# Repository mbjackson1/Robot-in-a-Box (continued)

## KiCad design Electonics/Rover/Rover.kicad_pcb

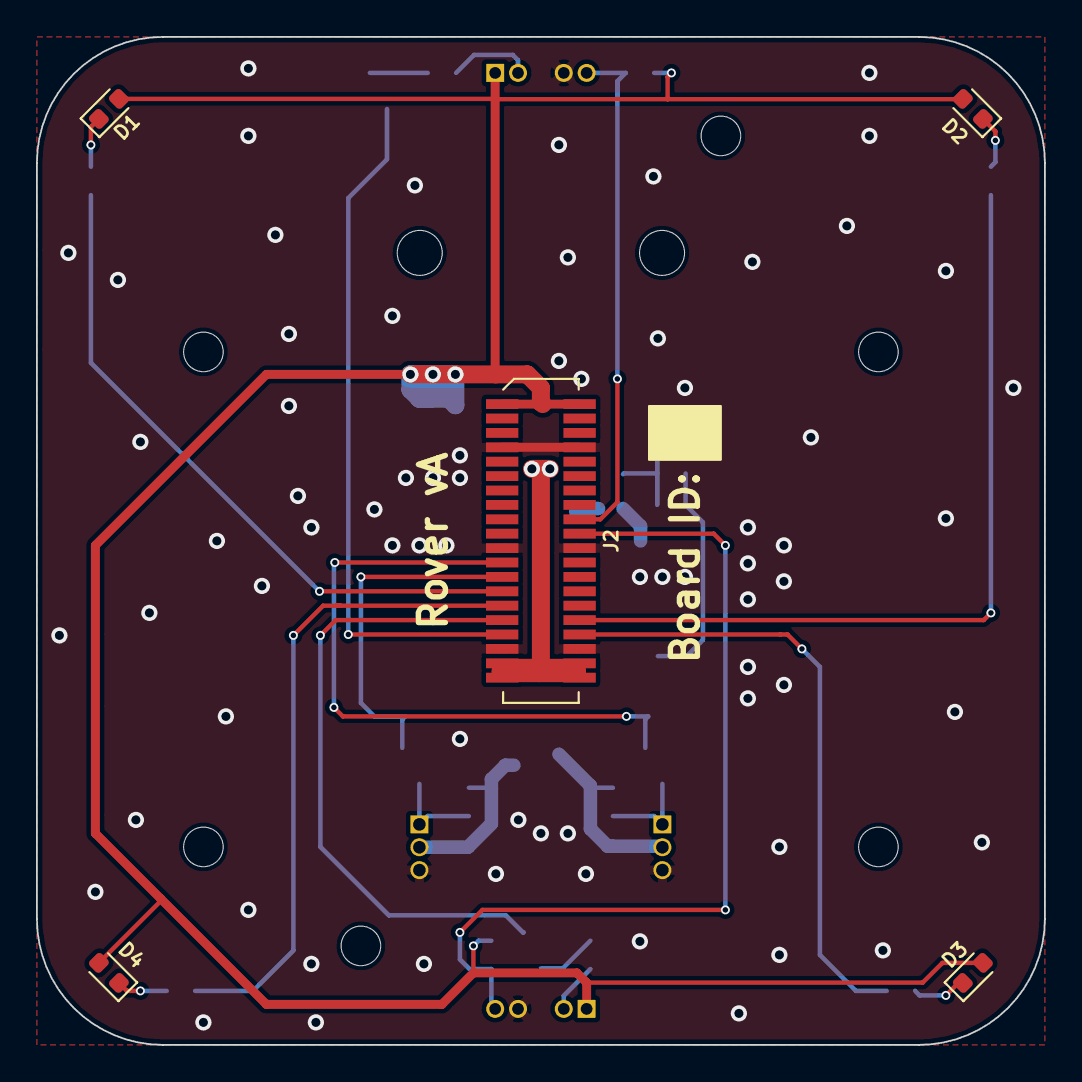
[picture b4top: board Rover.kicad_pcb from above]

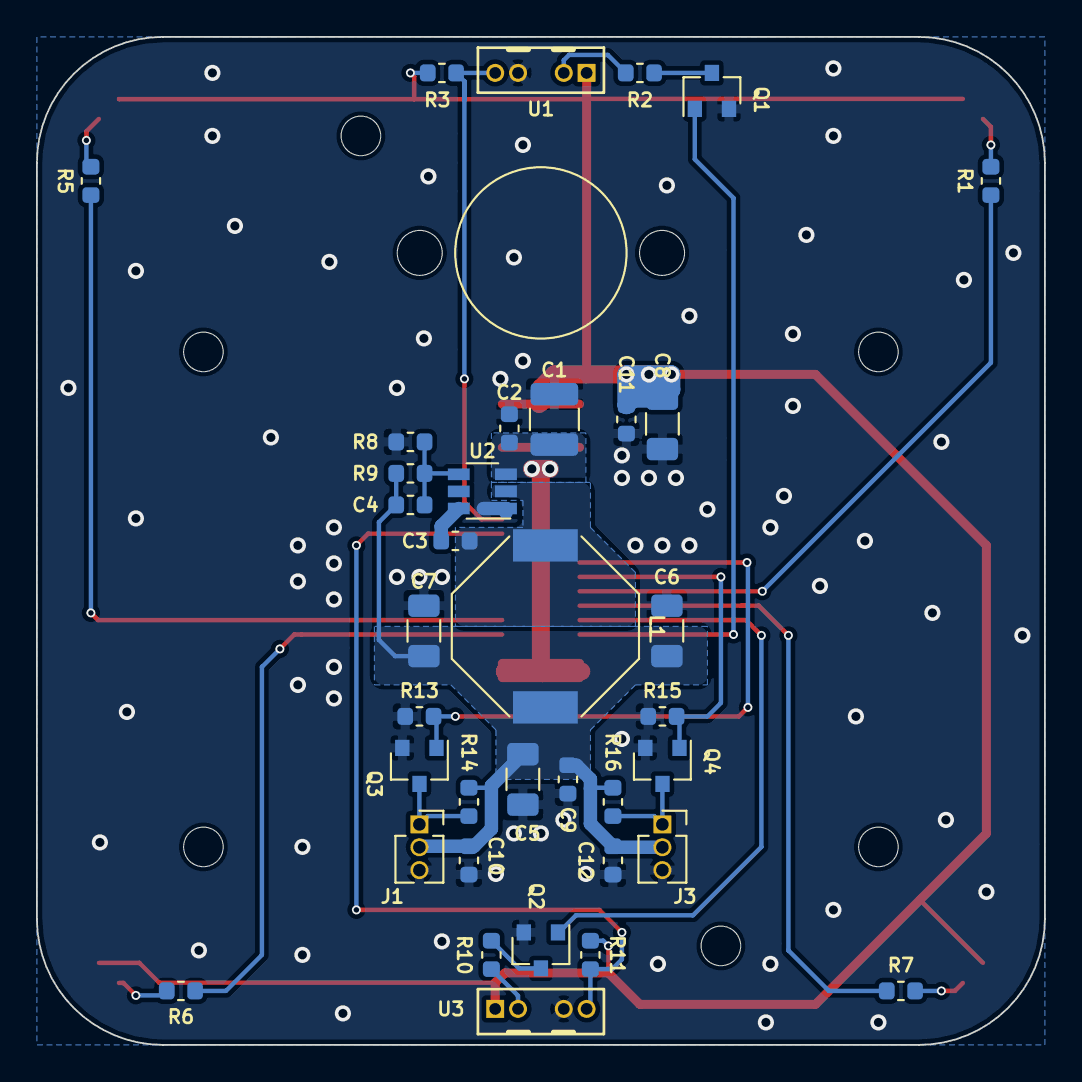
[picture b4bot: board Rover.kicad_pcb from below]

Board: 2 copper layers, 56.0 x 56.0 mm, 50 parts (40 on the bottom side), 27 nets.

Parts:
C1: 10uF; C_1210_3225Metric
C2, C3, C9, C10, C11, C12: 100nF; C_0603_1608Metric
C4: 100pF; C_0603_1608Metric
C5, C6, C7, C8: 22uF; C_1206_3216Metric
D1, D2, D3, D4: Green LED; LED_0603_1608Metric
H1, H2, H3, H4, H5, H6: M2; MountingHole_2.2mm_M2
J1, J3: Conn_01x03; PinSocket_1x03_P1.27mm_Vertical
J2: SlimStack 0.8mm 2x20; Molex_SlimStack_533074071_2x20_P0.8mm_Vertical_Female
L1: 15uH, 2.5A; L_Bourns-SRU1028_10.0x10.0mm
Q1, Q2, Q3, Q4: FDV303N; SOT-23
R1, R5, R6, R7: 100R; R_0603_1608Metric
R2, R10: 22R; R_0603_1608Metric
R3, R11, R13, R14, R15, R16: 10k; R_0603_1608Metric
R8: 12k; R_0603_1608Metric
R9: 100k; R_0603_1608Metric
T1: Rover vA; PCB_Title_&_Version
T2: Board ID; Board_Number
T3: Ball Caster; Pololu_Ball_Caster_9.5mm
U1, U3: TCRT1000; Vishay_TCRT10x0_Reflective_Sensor
U2: TPS54202; TSOT-23-6

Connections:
+3V3: C8.2, C11.2, D1.2, D2.2, D3.2, D4.2, J2.1, J2.2, R3.1, R11.1, U1.1, U3.1
+6V: C4.1, C5.2, C6.2, C7.2, C9.2, C10.2, C12.2, J1.2, J3.2, L1.2, R9.2, R14.2, R16.2
+12V: C1.2, C2.2, J2.37, J2.38, J2.39, J2.40, U2.3
/PC4: J2.18, R3.2, U1.4
/PC5: J2.20, R11.2, U3.4
/PD12: J2.31, Q2.1
/PD13: J2.33, Q1.1
/PD14: J2.32, R5.1
/PD15: J2.34, R6.1
/PE9: J2.23, Q3.1, R13.2
/PE11: J2.25, Q4.1, R15.2
/PE13: J2.27, R1.1
/PE14: J2.29, R7.1
GND: C1.1, C2.1, C5.1, C6.1, C7.1, C8.1, C9.1, C10.1, C11.1, C12.1, J1.3, J2.7, J2.8, J2.21, J2.22, J2.35, J2.36, J3.3, Q1.2, Q2.2, Q3.2, Q4.2, R8.2, R13.1, R15.1, U1.3, U2.1, U3.3
unnamed: C3.1, U2.6
unnamed: C3.2, L1.1, U2.2
unnamed: C4.2, R8.1, R9.1, U2.4
unnamed: D1.1, R1.2
unnamed: D2.1, R5.2
unnamed: D3.1, R6.2
unnamed: D4.1, R7.2
unnamed: J1.1, Q3.3, R14.1
unnamed: J3.1, Q4.3, R16.1
unnamed: Q1.3, R2.1
unnamed: Q2.3, R10.1
unnamed: R2.2, U1.2
unnamed: R10.2, U3.2

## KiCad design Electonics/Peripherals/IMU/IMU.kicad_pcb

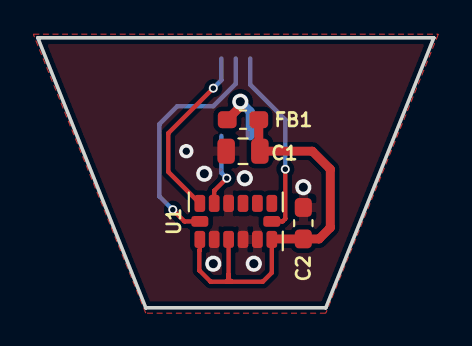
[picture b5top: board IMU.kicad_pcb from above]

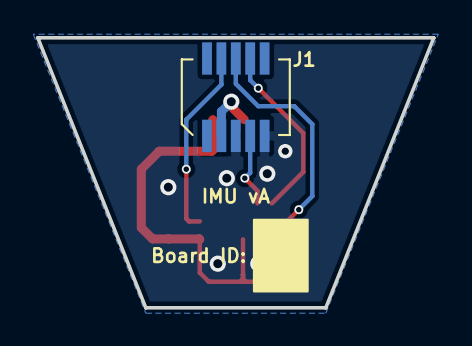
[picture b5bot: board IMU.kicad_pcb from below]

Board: 2 copper layers, 22.0 x 15.0 mm, 7 parts (2 on the bottom side), 7 nets.

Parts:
C1: 10uF; C_0805_2012Metric
C2: 100nF; C_0603_1608Metric_Pad1.05x0.95mm_HandSolder
FB1: 1k, 600mA; L_0603_1608Metric_Pad1.05x0.95mm_HandSolder
J1: Conn_01x10; Molex_SlimStack_533071071_2x05_P0.8mm_Vertical_Female
T1: IMU vA; PCB_Title_&_Version
T2: Board ID; Board_Number
U1: ADXL343; LGA-14_3x5mm_P0.8mm_LayoutBorder1x6y

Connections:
+3V3: FB1.1, J1.3
/GPIO(CS): J1.4, U1.7
/MISO: J1.7, U1.12
/MOSI: J1.8, U1.13
/SCK: J1.6, U1.14
GND: C1.1, C2.1, J1.5, J1.9, U1.2, U1.4, U1.5, U1.11
unnamed: C1.2, C2.2, FB1.2, U1.1, U1.3, U1.6

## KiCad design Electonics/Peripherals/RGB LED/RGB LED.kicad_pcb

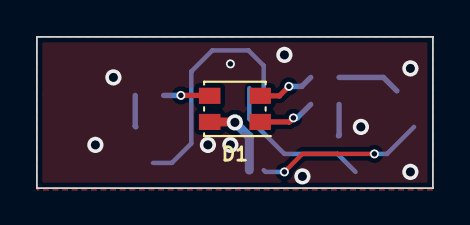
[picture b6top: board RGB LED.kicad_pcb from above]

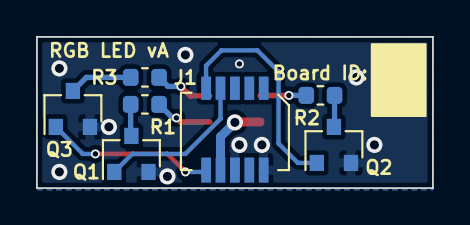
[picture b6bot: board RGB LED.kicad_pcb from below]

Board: 2 copper layers, 22.0 x 8.4 mm, 10 parts (8 on the bottom side), 11 nets.

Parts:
D1: RGB_LED; LED_Kingbright_AAA3528ESGCT
J1: Conn_01x10; Molex_SlimStack_533091070_2x05_P0.8mm_Right-Angle_Female
Q1, Q2, Q3: 2N7002; SOT-23
R1: 47R; R_0603_1608Metric
R2, R3: 22R; R_0603_1608Metric
T1: RGB LED vA; PCB_Title_&_Version
T2: Board ID; Board_Number

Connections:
+3V3: D1.2, J1.8
/ANALOG: J1.10, Q3.1
/GPIO(CS): J1.7, Q1.1
/TIMER: J1.9, Q2.1
GND: J1.2, J1.6, Q1.2, Q2.2, Q3.2
unnamed: D1.1, R1.1
unnamed: D1.3, R2.1
unnamed: D1.4, R3.1
unnamed: Q1.3, R1.2
unnamed: Q2.3, R2.2
unnamed: Q3.3, R3.2

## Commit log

2021-05-04 Forked from FYP repository to create public version of the design files. History starts at vA of boards, as released for manufacture as part of FYP.
2021-05-07 Corrected part information for USB
2021-07-13 Minor tidy-up of some of the files.
    Added set of instructions for setting up the library paths and BoM generation.
2021-07-13 Correction
